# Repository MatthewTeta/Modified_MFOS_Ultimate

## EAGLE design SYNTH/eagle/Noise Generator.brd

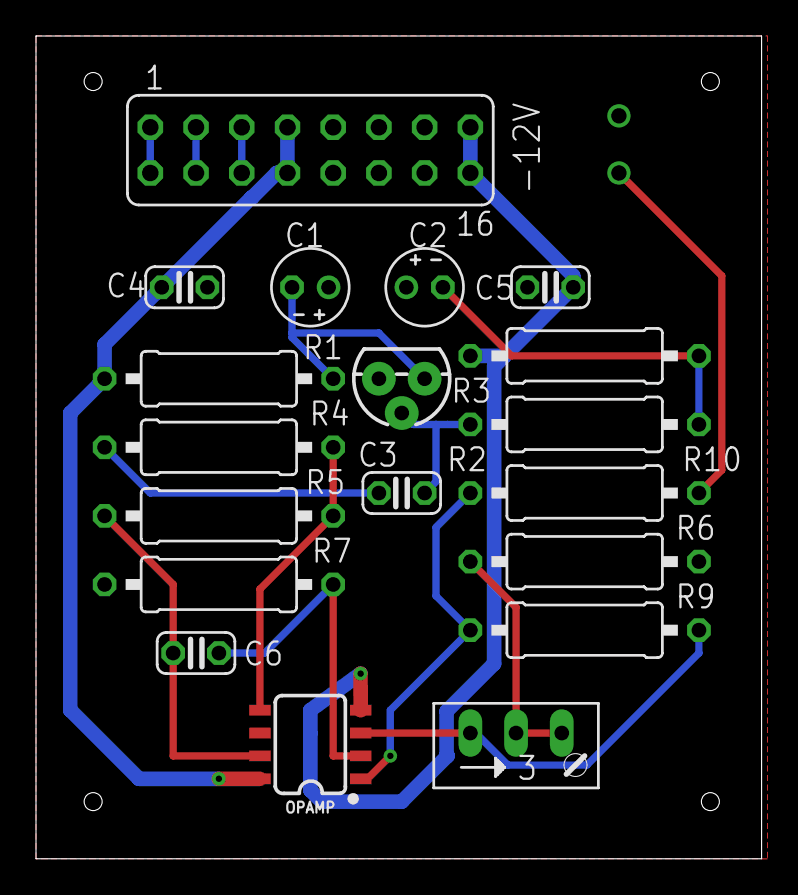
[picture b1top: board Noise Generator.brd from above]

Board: 2 copper layers, 40.3 x 45.7 mm, 19 parts (0 on the bottom side), 16 nets.

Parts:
C1, C2: 10uF; E2-4
C3, C4, C5, C6: .1uF; C025-024X044
OPAMP: TL072; SO08
Q1: 2N3904; TO-92
R1, R2, R3: 470k; 0309/12
R4: 20K; 0309/12
R5: 1M; 0309/12
R6: 1K; 0309/12
R7, R9: 100K; 0309/12
R8: 20K; RJ9W
R10: 3K; 0309/12
SV1: FE08-2

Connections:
+5V: SV1.5, SV1.6
+12V: C4.1, OPAMP.8, R1.2, SV1.7, SV1.8
-12V: C5.2, OPAMP.4, R3.1, SV1.15, SV1.16
CV: SV1.3, SV1.4
GATE: SV1.1, SV1.2
GND: C1.+, C2.+, C4.2, C5.1, OPAMP.6, R6.1, R7.1, SV1.9, SV1.10, SV1.11, SV1.12, SV1.13, SV1.14
unnamed: C2.-, R2.1, R3.2
unnamed: C1.-, Q1.1, R1.1
unnamed: R6.2, R8.A, R8.S
unnamed: C3.2, R4.1
unnamed: C3.1, Q1.2, R2.2
NEG1A: C6.2, OPAMP.2, R7.2
OUT1A: OPAMP.1, R9.2, R10.1
OUT1B: C6.1, OPAMP.7, R5.2
POS1A: OPAMP.3, R8.E, R9.1
POS1B: OPAMP.5, R4.2, R5.1

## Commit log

2017-06-13 added all my eagle files for the project
2017-06-13 Added my eagle files
2017-06-15 vco schematic

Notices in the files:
parts and their libraries:
SparkFun-DiscreteSemi: Licensing: Creative Commons ShareAlike 4.0 International - https://creativecommons.org/licenses/by-sa/4.0
